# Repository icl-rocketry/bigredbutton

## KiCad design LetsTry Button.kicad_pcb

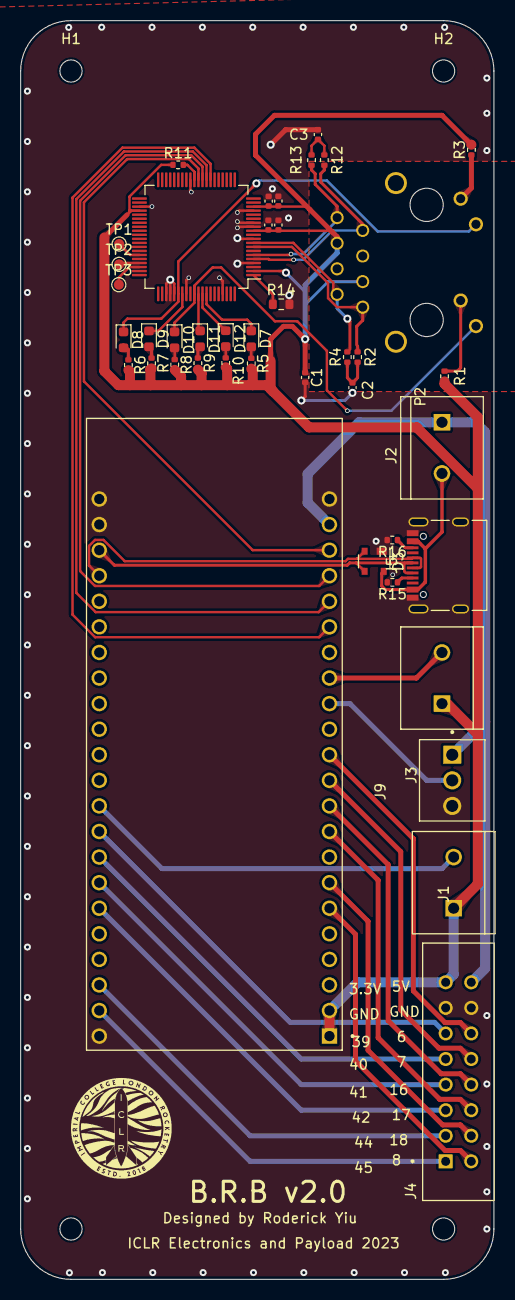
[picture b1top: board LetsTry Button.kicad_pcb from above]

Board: 2 copper layers, 47.0 x 125.0 mm, 46 parts (0 on the bottom side), 52 nets.

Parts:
C1, C2, C3: 0.1uF; C_0402_1005Metric
C4, C7: 10uF; C_0402_1005Metric
C5, C6: 100nF; C_0402_1005Metric
D3: SP0503BAHT; SOT-143
D7, D8, D9, D10, D11, D12: LED; LED_0603_1608Metric
H1, H2, H3, H4: MountingHole; MountingHole_2.2mm_M2
J1, J2, J9: Screw_Terminal_01x02; TE_282837-2
J3: Screw_Terminal_01x03; TE_282834-3
J4: 1658525-8; TE_1658525-8
J5: USB_C_Receptacle_USB2.0; USB_C_Receptacle_Palconn_UTC16-G
P2: RB1-125BAG1A; WIZNET_RB1-125BAG1A
R1, R3, R5, R6, R7, R8, R9, R10: 470; R_0402_1005Metric
R2, R4, R12, R13: 49.9; R_0402_1005Metric
R11: 10k; R_0402_1005Metric
R14: 12.3k; R_0603_1608Metric
R15, R16: 5.1k; R_0402_1005Metric
TP1, TP2, TP3: TestPoint; TestPoint_Pad_D1.0mm
U1: W5100; LQFP-80_10x10mm_P0.4mm
U2: ESP32-S3-DEVKITC-1-N8R2; XCVR_ESP32-S3-DEVKITC-1-N8R2

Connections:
+3.3V: C1.1, C4.1, C5.1, C6.1, C7.1, J1.1, J4.8, J9.1, P2.R3 (CT), P2.R6, R1.2, R3.2, R5.2, R6.2, R7.2, R8.2, R9.2, R10.2, R11.1, U1.2 (VCC3V3A), U1.12 (VCC3V3D), U1.18 (VCC3V3D), U1.44 (VCC3V3D), U2.J1_1 (3V3), U2.J1_2 (3V3)
+5V: J2.1, J3.1, J4.16, U2.J1_21 (5V0)
/W5100/COLLED: D11.1 (K), U1.71 (COLLED)
/W5100/CS: U1.29 (~SCS), U2.J1_19 (GPIO13)
/W5100/FDXLED: D10.1 (K), P2.L4, U1.70 (FDXLED)
/W5100/GPIO6: J4.9, U2.J1_6 (GPIO6)
/W5100/GPIO7: J4.10, U2.J1_7 (GPIO7)
/W5100/GPIO8: J4.14, U2.J1_12 (GPIO8)
/W5100/GPIO9: J9.2, U2.J1_15 (GPIO9)
/W5100/GPIO16: J4.11, U2.J1_9 (GPIO16)
/W5100/GPIO17: J4.12, U2.J1_10 (GPIO17)
/W5100/GPIO18: J4.13, U2.J1_11 (GPIO18)
/W5100/GPIO39: J4.6, U2.J3_9 (MTCK/GPIO39)
/W5100/GPIO40: J4.5, U2.J3_8 (MTDO/GPIO40)
/W5100/GPIO41: J4.4, U2.J3_7 (MTDI/GPIO41)
/W5100/GPIO42: J4.3, U2.J3_6 (MTMS/GPIO42)
/W5100/GPIO43: J4.1, U2.J3_2 (U0TXD/GPIO43)
/W5100/GPIO44: J4.2, U2.J3_3 (U0RXD/GPIO44)
/W5100/GPIO46: J3.2, U2.J1_14 (GPIO46)
/W5100/LINKLED: D8.1 (K), P2.L2, U1.66 (LINKLED)
/W5100/MISO: U1.27 (MISO), U2.J1_17 (GPIO11)
/W5100/MOSI: U1.28 (MOSI), U2.J1_18 (GPIO12)
/W5100/RXIN: P2.R8 (RD-), R12.2, U1.6 (RXIN)
/W5100/RXIP: P2.R7 (RD+), R13.2, U1.5 (RXIP)
/W5100/RXLED: D12.1 (K), U1.72 (RXLED)
/W5100/SCLK: U1.30 (SCLK), U2.J1_20 (GPIO14)
/W5100/SPDLED: D9.1 (K), U1.67 (SPDLED)
/W5100/TXLED: D7.1 (K), U1.73 (TXLED)
/W5100/TXON: P2.R2 (TD-), R4.2, U1.9 (TXON)
/W5100/TXOP: P2.R1 (TD+), R2.2, U1.8 (TXOP)
/W5100/USB D+: D3.2 (K), J5.A6 (D+), J5.B6 (D+), U2.J3_19 (USB_D+/GPIO20)
/W5100/USB D-: D3.3 (K), J5.A7 (D-), J5.B7 (D-), U2.J3_20 (USB_D-/GPIO19)
/W5100/VBUS: D3.4 (K), J2.2, J5.A4 (VBUS), J5.A9 (VBUS), J5.B4 (VBUS), J5.B9 (VBUS)
GND: C1.2, C2.1, C3.1, C4.2, C5.2, C6.2, C7.2, D3.1 (A), J3.3, J4.7, J4.15, J5.A1 (GND), J5.A12 (GND), J5.B1 (GND), J5.B12 (GND), J5.S1 (SHIELD), R14.2, R15.2, R16.2, U1.4 (GNDA), U1.10 (GNDA), U1.13 (GNDD), U1.14 (GNDD), U1.17 (GNDD), U1.32 (GNDD), U1.43 (GNDD), U1.63 (OPMODE0), U1.64 (OPMODE1), U1.65 (OPMODE2), U1.68 (GNDD), U1.77 (GNDA), U2.J1_22 (GND), U2.J3_1 (GND), U2.J3_21 (GND), U2.J3_22 (GND)
unnamed: C2.2, R2.1, R4.1
unnamed: C3.2, R12.1, R13.1
unnamed: D7.2 (A), R5.1
unnamed: D8.2 (A), R6.1
unnamed: D9.2 (A), R7.1
unnamed: D10.2 (A), R8.1
unnamed: D11.2 (A), R9.1
unnamed: D12.2 (A), R10.1
unnamed: J1.2, U2.J3_10 (GPIO38)
unnamed: J5.A5 (CC1), R15.1
unnamed: J5.B5 (CC2), R16.1
unnamed: P2.L1, R3.1
unnamed: P2.L3, R1.1
unnamed: R14.1, U1.1 (RSET_BG)
unnamed: R11.2, U1.31 (SEN)
unnamed: TP1.1, U1.55 (~CS)
unnamed: TP3.1, U1.58 (~RD)
unnamed: TP2.1, U1.57 (~WR)

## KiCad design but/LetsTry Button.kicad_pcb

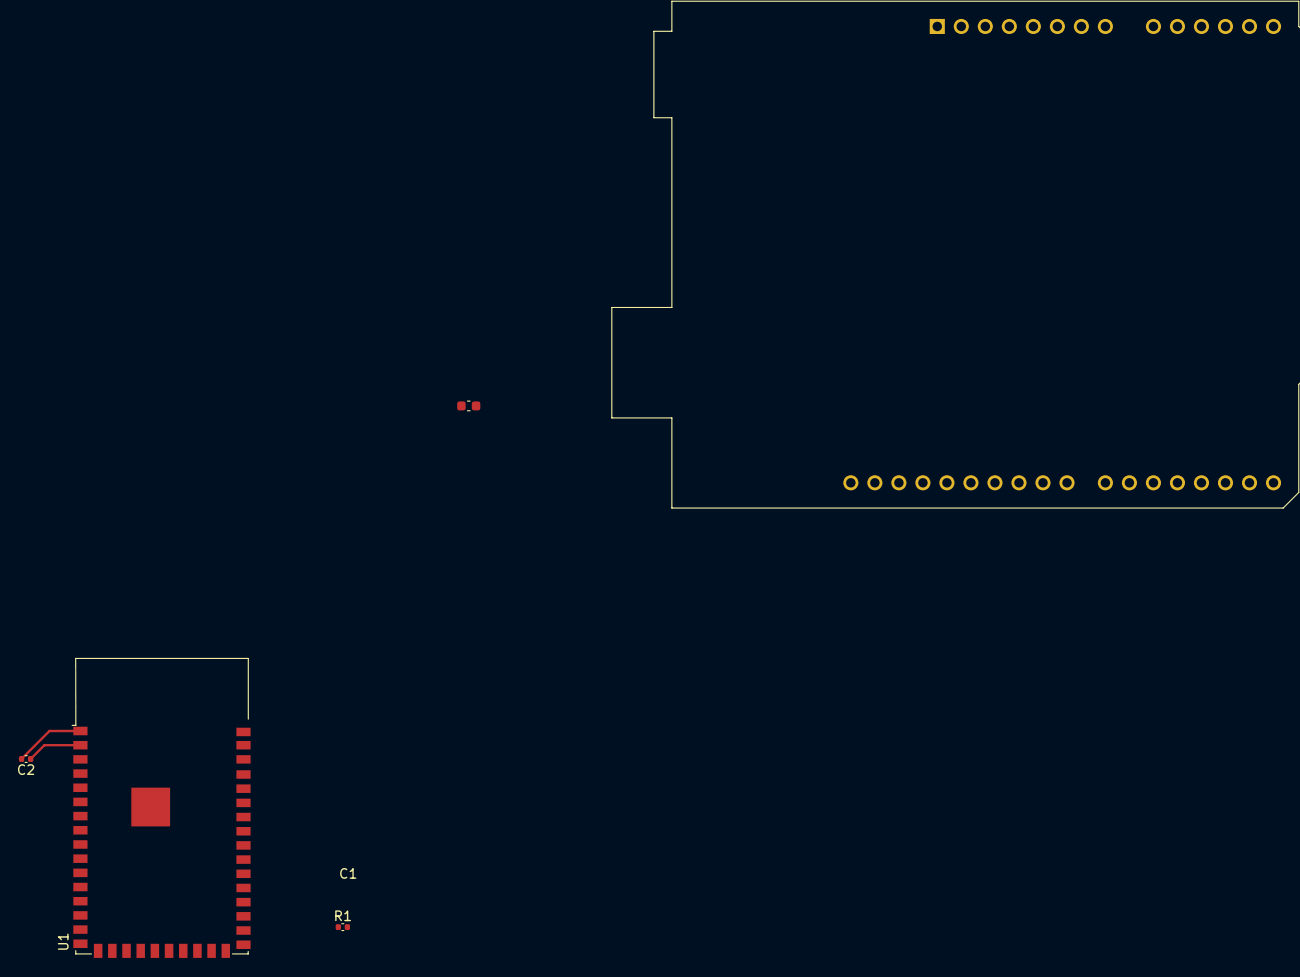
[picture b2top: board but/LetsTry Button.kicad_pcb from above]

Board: 2 copper layers, 5 parts (0 on the bottom side), 3 nets.

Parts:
A1: Arduino_UNO_R3
C1: 22uF; C_0603_1608Metric
C2: 0.1uF; C_0402_1005Metric
R1: 1000; C_0402_1005Metric
U1: ESP32-S2-WROVER

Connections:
GND: C1.2, C2.2, U1.1 (GND), U1.26 (GND), U1.42 (GND), U1.43 (GND)
unnamed: R1.2, U1.15 (IO12)
VDD: C1.1, C2.1, U1.2 (3V3)

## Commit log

2023-06-28 putting my files in
2023-07-29 Add files via upload
    number 2
2023-08-02 Add files via upload
    usbc
2023-08-08 Add files via upload
    New one, idk if TVS diode is right
2023-08-08 Add files via upload
    the new one
2023-08-08 Add files via upload
    even new
2023-08-10 Add files via upload
    fixed
2023-08-13 i fimally learnt how to use github
2023-08-13 i finally learnt how to use github. Final Buttton?
2023-09-05 ordering
